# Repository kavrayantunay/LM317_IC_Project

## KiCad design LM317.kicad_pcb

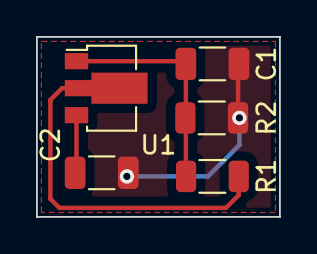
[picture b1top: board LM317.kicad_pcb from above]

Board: 2 copper layers, 13.5 x 10.0 mm, 5 parts (0 on the bottom side), 4 nets.

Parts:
C1: 1uF; C_1206_3216Metric
C2: 0.1uF; C_1206_3216Metric
R1: 240; R_1206_3216Metric
R2: 1k; R_1206_3216Metric
U1: LM317L_SOT-89; SOT-89-3

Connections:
/vin: C2.1, U1.3 (VI)
/vout: C1.1, R1.2, R2.2, U1.1 (ADJ)
GND: C1.2, C2.2, R2.1
unnamed: R1.1, U1.2 (VO)
